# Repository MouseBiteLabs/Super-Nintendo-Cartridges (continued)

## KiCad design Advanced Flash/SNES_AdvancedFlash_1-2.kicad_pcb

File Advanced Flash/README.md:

# Super Nintendo Advanced Flash Cartridge (SNES-8XJ4D-01A)

# Order at your own risk -- v1.2 is technically untested, but previous version is fully tested

This is a new and improved Super Nintendo cartridge circuit board design that is capable of being flashed via the <a href="https://github.com/sanni/cartreader">Open Source Cart Reader (OSCR) by sanni</a>. Alternatively, you can also flash the ROM chips before soldering them to the board through the use of a programmer like the <a href="https://xgecu.myshopify.com/products/xgecu-new-t48-tl866-3gprogrammer-v12-01-support-28000-ics-for-spi-nor-nand-flash-emmc-bga153-162-169-100-221-tsop-sop-plcc">T48 programmer</a> with the <a href="https://xgecu.myshopify.com/products/100-original-xgecu-adp_f48_ex-1-tsop48-special-adapter-for-nor-flash-only-use-on-t48-tl866-3g-programmer">TSOP48 adapter</a>. This cartridge is made entirely from **brand new off the shelf components.** No donors are required, and you don't need to rely on AliExpress or eBay for parts!

This cartridge covers over 95% of the entire SNES library, capable of any standard cartridge **but not those with co-processors, such as SA-1 or SuperFX.** You can backup games onto it with the following settings:
- All memory maps supported: LoROM, HiROM, ExLoROM, and ExHiROM
- Can be programmed to operate as a multicart, changing games by pressing the SNES reset button (this includes the ability to make two games of the same memory map, or one of each)
- Up to 8 MB of ROM space for a single game or 4 MB of ROM space for two games
- Up to 32 KB of RAM space for a single game or two separate banks of 32 KB RAM space for two games
- All these settings can be changed via DIP switch for easy on-the-fly modifications without soldering

All gerbers and source files can be found in this repo, as this project is fully open source. Please read all instructions before attempting the project.

## Important Things Before You Start

1) <a href="https://github.com/MouseBiteLabs/Super-Nintendo-Cartridges/wiki">Please review the wiki for more information about using the circuit boards, instructions for how to program them, and example builds.</a>
2) When soldering parts on, it's a good idea to put kapton tape or otherwise cover the bottom cartridge edge. You do not want to get solder on the cartridge contacts.
3) I am not responsible for any damage you do to your self or your property. Attempt this project at your own risk.
4) I do not guarantee design compatibility. You may encounter issues with certain games. There is also a chance I have made an error in the design or the BOM - if this is the case, I will do everything I can to address the problem as quickly as possible.
5) If you are using this board to make games other than for personal use, you must have permission from the originator to use and distribute any ROM images or other related material. You are responsible for making sure you adhere to any license requirements.

DO NOT use my circuit boards for profiting from stolen work - this especially includes homebrew content, ROM hacks, and using fan-made labels without permission from the originator. **Support ALL original creators!**

## Board Characteristics and Order Information

The zipped folder contains all the gerber files for this board. The following options **must** be chosen when ordering boards for yourself.

- Thickness: 1.2mm
- Surface Finish: ENIG
- Gold Fingers: Yes, 30° chamfer

You can use the zipped folder at any board fabricator you like. You may also buy the board from PCBWay using this link (disclosure: I receive 10% of the sale value to go towards future PCB orders of my own):

### Purchase from My Website

You can purchase this circuit board at my website, [https://mousebitelabs.store](https://mousebitelabs.store). Click the following image to be directed to the specific item listing:

### Purchase from Etsy

I also offer the board on Etsy, if you would rather purchase through there - click the banner to be redirected.

### Purchase from insideGadgets

And finally, insideGadgets sells these boards fully populated!

## Required Equipment

- You will need basic tools, like a soldering iron, hot plate, and/or hot air rework station.
- You need a way to program the ROM chip(s).
  - This can be done with the <a href="https://github.com/sanni/cartreader">OSCR</a> to load the game and save data onto the catridge, after the cartridge is assembled.
  - Another option is to use insideGadgets' <a href="https://shop.insidegadgets.com/product/snesxflasher/">SNES programmer</a> made specifically for my cartridges. <a href="https://shop.insidegadgets.com/product/snes-advanced-flash-cartridge/">You can even purchase assembled boards from them!</a>
  - Alternatively, the <a href="https://xgecu.myshopify.com/products/xgecu-new-t48-tl866-3gprogrammer-v12-01-support-28000-ics-for-spi-nor-nand-flash-emmc-bga153-162-169-100-221-tsop-sop-plcc">T48 programmer</a> with the <a href="https://xgecu.myshopify.com/products/100-original-xgecu-adp_f48_ex-1-tsop48-special-adapter-for-nor-flash-only-use-on-t48-tl866-3g-programmer">TSOP48 adapter</a> can program the ROM chip(s). The downside to this is that if you screw up the programming, you'll have to desolder the chips and program them again.
- This cartridge uses the PIC12F629 with the <a href="https://sd2snes.de/blog/cool-stuff/supercic">SuperCIC code</a> to fake out the lockout chip. You will need a way to program these PIC chips. I use the T48 to do so, but you can also use something like the <a href="https://www.microchip.com/en-us/development-tool/pg164130">PICkit 3.</a> Note that if you have region modded your SNES, you won't need the lockout chips in the cartridges.

## How to Program

<a href="https://github.com/MouseBiteLabs/Super-Nintendo-Cartridges/wiki/Preparing-the-ROM">Please check out the wiki pages on how to prepare the ROM and program the cartridge.</a>

## Board Configurations

You *do not* need every single part on this board to make a game. The game you want to make is mainly dependent on the memory mapping (LoROM, HiROM, etc), the ROM size, and the RAM size. Depending on your needs, you only need to solder on certain components, which you can find below in the BOM section.

- **Every board needs Group A components.** You can make LoRom or HiROM games that have no RAM and are up to 4 MB large with this configuration. (If your game is only 2 MB, you do not need to include U9 and C9)
- If you need RAM space, **add Group B components.** This will add 32 KB of RAM space. (Multicarts will need the AS6C1008 chip for the RAM)
- If your game is larger than 4 MB, it will use the ExLoROM or ExHiROM memory mapping. **Add Group C components for this.**
- For multicarts, you can make a board with two games on it up to 4 MB each. You will need Group C components, **as well as Group D components.** (If one of the two games you want to program is only 2 MB, you do not need to include U9 and C9 for Game 1, and/or U12 and C12 for Game 2.)

## Switches

For SW1 through SW5, you can either use the DIP switch as indicated in the BOM below (in the "Optional" sections), or you can jumper the pads underneath the switch to turn the switch "ON". In this example, positions 1 and 2 are "ON"; 3 and 4 are "OFF":

### Switch 1 - Memory Mapping

This is the LoROM/HiROM switch. Turn it on to enter LoROM mode, or turn it off for HiROM mode, depending on the game you program.

### Switch 2 - SRAM Size

This sets the RAM size for the game, assuming you have the RAM chip installed. The maximum allocated RAM space *per game* on this board is only 32 KB, even if you put a 128 KB RAM chip (you will need the 128 KB chip for multicarts). Some games will care that you have the correct RAM size, or else they will activate piracy protection, so you should try to match the settings your game calls for. Note that DIP positions 1/2, and 3/4 should be changed together simultaneously:

- For 2 KB of RAM, set all switches OFF.
- For 8 KB of RAM, set positions 1 and 2 ON, and 3 and 4 OFF.
- For 32 KB of RAM, set all positions ON.

*Note: If you have a v1.1 board, please read the section below, as the instructions are slightly different to set the RAM size correctly.*

### Switch 3 - Ex Mode

Switch this ON to change the setting on SW1 to ExLoROM/ExHiROM. Switch it OFF to keep SW1 as a LoROM/HiROM switch.

### Switch 4 and 5 - Multicart Configurations

These two sets of switches control the multicart features on the board. You can make two LoROM games, two HiROM games, or one LoROM game and one HiROM game if you set the "Map Swap" switch to "YES". Here is how to use the switches to program the two games:

- Set SW4B (MULTI MODE) to "PRG" (for programming)
- Put SW4A (MAP SWAP) in the mode you want to use:
  - YES = Game 1 is LoROM, Game 2 is HiROM
  - NO = Game 1 and Game 2 are both LoROM or HiROM depending on SW1 position
  - If you are programming two of the same memory map types, put SW1 into the desired memory map mode (SW1 position does not matter if you are using the map swap feature)
- Program the first game by putting SW5 in "GAME 1" position; program the second by putting SW5 in "GAME 2" position
  - If you are going to use the map swap feature, make sure game 1 is the LoROM game and game 2 is the HiROM game!
- After both games are programmed, set SW4B to "PLAY"

Note that if you keep SW4B in "PRG" mode, the game that boots up will be determined by the position of SW5.

## Fix for v1.1

There's a minor issue with v1.1 of the board. **This does not affect versions after v1.1.** 

For setting the SRAM size using SW2, you must do the following:

- For 2 KB of RAM, set all switches OFF.
- For 8 KB of RAM, set positions 1 and 2 ON, and 3 and 4 OFF. **REMOVE R8 AND R9 FROM THE BOARD.**
- For 32 KB of RAM, set all positions ON. **REMOVE R8, R9, R10, AND R11 FROM THE BOARD.**

If you *do not* remove the resistors as defined above, your save battery life will be severely impacted. 

### Multicarts for v1.1

You *cannot* make multicarts on v1.1.

## Estimating Battery Life

To accurately estimate the battery life, you must first solder the battery in, and then either program your game in the OSCR or power it on in a Super Nintendo.

After that, measure the voltage across R1 using a multimeter in DC mV mode, touching the probes to the two test point pads on either side of R1 (or, the + and - pads on the back of the board below my smiling face). You should read something around 10 mV or less. If you are severely higher than 10 mV, like in the 100's of mV, then you have a problem on your board.

Once you have a suitable voltage, find the milliamp-hour rating of your selected battery (preferrably from a datasheet). For example, a Renata CR2032 battery is rated for 225 mAh.

Now to estimate battery life, take the voltage measurement in mV and the battery rating in mAh, and plug it into this equation: 

Time (years) = Resistance of R1 (ohms) * Battery capacity (mAh) / Voltage (mV) / 8760

The factor of 8760 is for converting years to hours (24 hours in a day, 365 days in a year). The resistance of R1 is 10000 ohms. So for an example, if you measured 10 mV on R1 and are using a Renata CR2032, you would get 10000 * 225 / 10 / 8760 = **25.7 years.**

## Troubleshooting

<a href="https://github.com/MouseBiteLabs/Super-Nintendo-Cartridges/wiki/Troubleshooting-Tips">Please check out the wiki pages for troubleshooting tips.</a>

## Bill of Materials (BOM)

The component groups required for the build you want to make are detailed above. Note that the "optional" groups mostly only contain the switches, as you can manually set the switch position with a 0-ohm resistor (or, lack of a resistor). Remember, shorting the pads means the switch is ON, and keeping the pads depopulated means the switch is OFF.

### Mouser Shopping Cart

The following cart has *the maximum amount* of parts you would potentially need on a single board (essentially, a multicart), plus a few extras of the passive components due to price breaks. This also includes **four M29F160 chips and both the AS6C62256 and AS6C1008.** You can remove the chips you don't need from the shopping cart before ordering, according to the component group assignments below.

https://www.mouser.com/ProjectManager/ProjectDetail.aspx?AccessID=1bc68cfc83

### Group A - 4 MB ROM, No RAM

Note: If your game is only 2 MB, you do not need U9 and C9.

| Reference | Value/Part Number | Package       | Description      | Source                                           |
| --------- | ----------------- | ------------- | ---------------- | ------------------------------------------------ |
| C1        | 0.1u              | 0603          | Capacitor (MLCC) | [https://mou.sr/3ENc15O](https://mou.sr/3ENc15O) |
| C2        | 0.1u              | 0603          | Capacitor (MLCC) | [https://mou.sr/3ENc15O](https://mou.sr/3ENc15O) |
| C3        | 0.1u              | 0603          | Capacitor (MLCC) | [https://mou.sr/3ENc15O](https://mou.sr/3ENc15O) |
| C4        | 0.1u              | 0603          | Capacitor (MLCC) | [https://mou.sr/3ENc15O](https://mou.sr/3ENc15O) |
| C7        | 0.1u              | 0603          | Capacitor (MLCC) | [https://mou.sr/3ENc15O](https://mou.sr/3ENc15O) |
| C8        | 0.1u              | 0603          | Capacitor (MLCC) | [https://mou.sr/3ENc15O](https://mou.sr/3ENc15O) |
| C9        | 0.1u              | 0603          | Capacitor (MLCC) | [https://mou.sr/3ENc15O](https://mou.sr/3ENc15O) |
| CC        | 22u               | 1206          | Capacitor (MLCC) | [https://mou.sr/4e4zShm](https://mou.sr/4e4zShm) |
| R2        | 100k              | 0603          | Resistor         | [https://mou.sr/49bgMnu](https://mou.sr/49bgMnu) |
| R3        | 10k               | 0603          | Resistor         | [https://mou.sr/3riR7IH](https://mou.sr/3riR7IH) |
| R4        | 100k              | 0603          | Resistor         | [https://mou.sr/49bgMnu](https://mou.sr/49bgMnu) |
| R5        | 10k               | 0603          | Resistor         | [https://mou.sr/3riR7IH](https://mou.sr/3riR7IH) |
| U1        | PIC12F629         | DIP-8, SOIC-8 | Lockout Chip     | [https://mou.sr/3XuEZzO](https://mou.sr/3XuEZzO) |
| U2        | SN74CBT3257CPWR   | TSSOP-16      | Multiplexer      | [https://mou.sr/3MKJwd1](https://mou.sr/3MKJwd1) |
| U3        | SN74CBT3257CPWR   | TSSOP-16      | Multiplexer      | [https://mou.sr/3MKJwd1](https://mou.sr/3MKJwd1) |
| U4        | SN74CBT3257CPWR   | TSSOP-16      | Multiplexer      | [https://mou.sr/3MKJwd1](https://mou.sr/3MKJwd1) |
| U7        | 74HCT139          | TSSOP-16      | Decoder          | [https://mou.sr/4eqzppn](https://mou.sr/4eqzppn) |
| U8        | M29F160           | TSOP-48       | Flash EEPROM     | [https://mou.sr/3MNWQ0b](https://mou.sr/3MNWQ0b) |
| U9        | M29F160           | TSOP-48       | Flash EEPROM     | [https://mou.sr/3MNWQ0b](https://mou.sr/3MNWQ0b) |

### Group A (Optional) - Programming header, Lo/Hi switch/jumper

Note: J1 is a space that allows you to program the PIC using the standard ISP pinout while the chip is on-board. It is not a required component. If you wish to use it, you will need to pick out a component yourself to use here, as there are different ways to go about using it.

| Reference | Value/Part Number   | Package                  | Description        | Source                                           |
| --------- | ------------------- | ------------------------ | ------------------ | ------------------------------------------------ |
| J1        | \--                 | 2x3 pins, 2.54mm spacing | Header (see note)  | N/A                                              |
| RS1       | 0 ohm               | 0603                     | Resistor (Jumper)  | [https://mou.sr/4e1ABQg](https://mou.sr/4e1ABQg) |
| SW1       | DS04-254-2-01BK-SMT | 1-position DIP           | DIP Switch (1-pos) | [https://mou.sr/3MK4Lvz](https://mou.sr/3MK4Lvz) |

### Group B - adds 32 KB of RAM

Note: If you are making a multicart, you must use the AS6C1008 for U10.

| Reference | Value/Part Number   | Package        | Description        | Source                                           |
| --------- | ------------------- | -------------- | ------------------ | ------------------------------------------------ |
| B1        | CR2032              | CR2032         | Coin Cell Battery  | [https://mou.sr/3Wj2m0G](https://mou.sr/3Wj2m0G) |
| C5        | 0.1u                | 0603           | Capacitor (MLCC)   | [https://mou.sr/3ENc15O](https://mou.sr/3ENc15O) |
| C6        | 0.1u                | 0603           | Capacitor (MLCC)   | [https://mou.sr/3ENc15O](https://mou.sr/3ENc15O) |
| C10       | 0.1u                | 0603           | Capacitor (MLCC)   | [https://mou.sr/3ENc15O](https://mou.sr/3ENc15O) |
| C11       | 0.1u                | 0603           | Capacitor (MLCC)   | [https://mou.sr/3ENc15O](https://mou.sr/3ENc15O) |
| CB        | 22u                 | 1206           | Capacitor (MLCC)   | [https://mou.sr/4e4zShm](https://mou.sr/4e4zShm) |
| Q1        | 2N7002              | SOT-23         | N-channel MOSFET   | [https://mou.sr/3rgfh6J](https://mou.sr/3rgfh6J) |
| R1        | 10k                 | 0603           | Resistor           | [https://mou.sr/3riR7IH](https://mou.sr/3riR7IH) |
| R6        | 130k                | 0603           | Resistor           | [https://mou.sr/3MjXliy](https://mou.sr/3MjXliy) |
| R7        | 49.9k               | 0603           | Resistor           | [https://mou.sr/3BBcDgp](https://mou.sr/3BBcDgp) |
| R8        | 100k                | 0603           | Resistor           | [https://mou.sr/49bgMnu](https://mou.sr/49bgMnu) |
| R9        | 100k                | 0603           | Resistor           | [https://mou.sr/49bgMnu](https://mou.sr/49bgMnu) |
| R10       | 100k                | 0603           | Resistor           | [https://mou.sr/49bgMnu](https://mou.sr/49bgMnu) |
| R11       | 100k                | 0603           | Resistor           | [https://mou.sr/49bgMnu](https://mou.sr/49bgMnu) |
| U5        | 74HCT139            | TSSOP-16       | Decoder            | [https://mou.sr/4eqzppn](https://mou.sr/4eqzppn) |
| U6        | 74HCT139            | TSSOP-16       | Decoder            | [https://mou.sr/4eqzppn](https://mou.sr/4eqzppn) |
| U10       | AS6C62256, AS6C1008 | SOP-28, SOP-32 | SRAM               | [https://mou.sr/3ZxG6jd](https://mou.sr/3ZxG6jd) |
| U11       | TPS3613             | MSOP-10        | Battery Management | [https://mou.sr/45Ir2kh](https://mou.sr/45Ir2kh) |

### Group B (Optional) - RAM size switch/jumpers

| Reference | Value/Part Number   | Package        | Description        | Source                                           |
| --------- | ------------------- | -------------- | ------------------ | ------------------------------------------------ |
| RS2A      | 0 ohm               | 0603           | Resistor (Jumper)  | [https://mou.sr/4e1ABQg](https://mou.sr/4e1ABQg) |
| RS2B      | 0 ohm               | 0603           | Resistor (Jumper)  | [https://mou.sr/4e1ABQg](https://mou.sr/4e1ABQg) |
| RS2C      | 0 ohm               | 0603           | Resistor (Jumper)  | [https://mou.sr/4e1ABQg](https://mou.sr/4e1ABQg) |
| RS2D      | 0 ohm               | 0603           | Resistor (Jumper)  | [https://mou.sr/4e1ABQg](https://mou.sr/4e1ABQg) |
| SW2       | DS04-254-2-04BK-SMT | 4-position DIP | DIP Switch (4-pos) | [https://mou.sr/3MPsI4o](https://mou.sr/3MPsI4o) |

### Group C - Adds 4 MB ROM for ExLoROM and ExHiROM

Note: If your Ex-mode game is 6 MB large, you don't need U13 and C13.

| Reference | Value/Part Number | Package | Description      | Source                                           |
| --------- | ----------------- | ------- | ---------------- | ------------------------------------------------ |
| C12       | 0.1u              | 0603    | Capacitor (MLCC) | [https://mou.sr/3ENc15O](https://mou.sr/3ENc15O) |
| C13       | 0.1u              | 0603    | Capacitor (MLCC) | [https://mou.sr/3ENc15O](https://mou.sr/3ENc15O) |
| U12       | M29F160           | TSOP-48 | Flash EEPROM     | [https://mou.sr/3MNWQ0b](https://mou.sr/3MNWQ0b) |
| U13       | M29F160           | TSOP-48 | Flash EEPROM     | [https://mou.sr/3MNWQ0b](https://mou.sr/3MNWQ0b) |

### Group C (Optional) - Ex Mode switch/jumper

| Reference | Value/Part Number   | Package        | Description        | Source                                           |
| --------- | ------------------- | -------------- | ------------------ | ------------------------------------------------ |
| RS3       | 0 ohm               | 0603           | Resistor (Jumper)  | [https://mou.sr/4e1ABQg](https://mou.sr/4e1ABQg) |
| SW3       | DS04-254-2-01BK-SMT | 1-position DIP | DIP Switch (1-pos) | [https://mou.sr/3MK4Lvz](https://mou.sr/3MK4Lvz) |

### Group D - Enables multicart mode

Note: If your game(s) are 2 MB, you do not need U9 and C9 (for Game 1) and/or U12 and C12 (for Game 2).

| Reference | Value/Part Number | Package   | Description      | Source                                           |
| --------- | ----------------- | --------- | ---------------- | ------------------------------------------------ |
| C14       | 0.1u              | 0603      | Capacitor (MLCC) | [https://mou.sr/3ENc15O](https://mou.sr/3ENc15O) |
| R13       | 1k                | 0603      | Resistor         | [https://mou.sr/3U0EvS4](https://mou.sr/3U0EvS4) |
| U14       | 74HCT74           | TSSOP-14  | Flip-Flop        | [https://mou.sr/4eroZpu](https://mou.sr/4eroZpu) |

### Group D (Optional) - Multicart mode switches/jumpers

| Reference | Value/Part Number   | Package        | Description        | Source                                           |
| --------- | ------------------- | -------------- | ------------------ | ------------------------------------------------ |
| RS4A      | 0 ohm               | 0603           | Resistor (Jumper)  | [https://mou.sr/4e1ABQg](https://mou.sr/4e1ABQg) |
| RS4B      | 0 ohm               | 0603           | Resistor (Jumper)  | [https://mou.sr/4e1ABQg](https://mou.sr/4e1ABQg) |
| RS5       | 0 ohm               | 0603           | Resistor (Jumper)  | [https://mou.sr/4e1ABQg](https://mou.sr/4e1ABQg) |
| SW4       | DS04-254-2-02BK-SMT | 2-position DIP | DIP Switch (2-pos) | [https://mou.sr/3B7BqZr](https://mou.sr/3B7BqZr) |
| SW5       | DS04-254-2-01BK-SMT | 1-position DIP | DIP Switch (1-pos) | [https://mou.sr/3MK4Lvz](https://mou.sr/3MK4Lvz) |

## Revision History

### v1.2 - Release

- Fixed C9 and C12 positions on PCB
- Added resistors under all switches as alternative
- Changed R8 through R11 to pull-down resistors
- Added Q1 to ensure RAM start-up at correct time
- Simplified multicart circuit to reduce battery current draw, lower the BOM count/cost and simplify the design
- Remove "1" from single DIP switches for clarity

### v1.1 - Beta

- Change reference designators CC1 to CC, CB1 to CB
- Make silkscreen thicker, pin 1 indicators bigger, add boxes around passives
- Round the cart edge for easier insertion, add cart edge pin numbers
- Add pin 1 indicators to switches and U1; move U2-U7 reference designators
- Change Prog/Play to more descriptive language
- Add pads for resistors instead of switches

### v1.0 - Alpha

- Prototype version

## Acknowledgements

- Extremely huge thanks to sanni for firstly creating the OSCR, and secondly for adding programming support for the cartridges.
- Continual thanks to all in the nesdev community for their resources, design tips, and support throughout the past half-decade.

## License

<br />This work is licensed under a <a rel="license" href="http://creativecommons.org/licenses/by-sa/4.0/">Creative Commons Attribution-ShareAlike 4.0 International License</a>. You are able to copy and redistribute the material in any medium or format, as well as remix, transform, or build upon the material for any purpose (even commercial) - but you **must** give appropriate credit, provide a link to the license, and indicate if any changes were made.

©MouseBiteLabs 2024

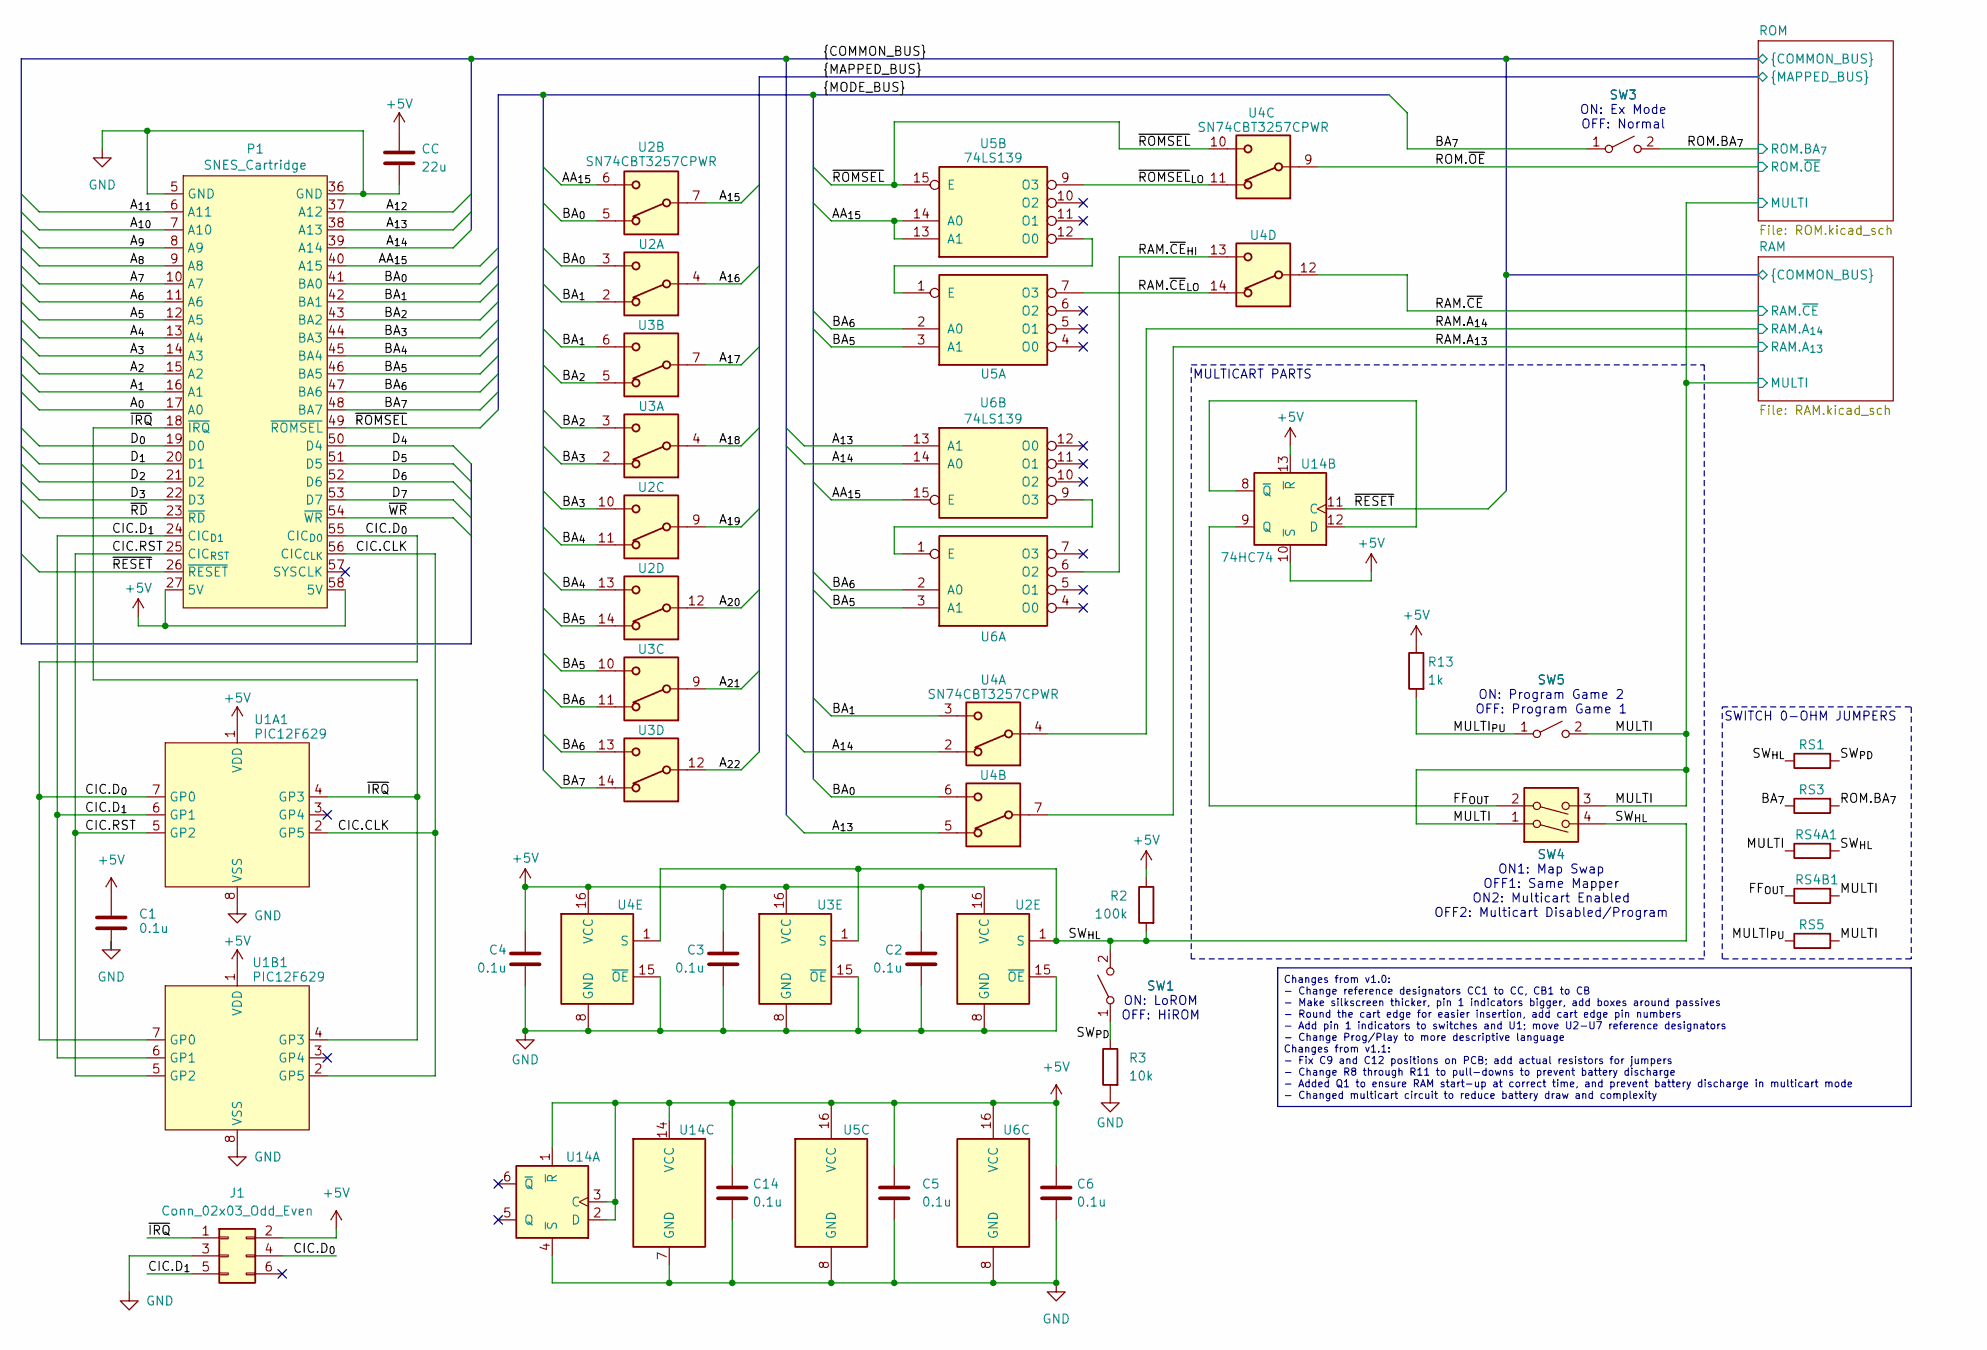
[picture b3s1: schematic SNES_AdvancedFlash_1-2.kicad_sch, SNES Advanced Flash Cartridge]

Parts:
C1, C2, C3, C4, C5, C6, C14: 0.1u; C_0603_1608Metric_Boxed
CC: 22u; C_1206_3216Metric_Boxed
J1: Conn_02x03_Odd_Even; PinHeader_2x03_P2.54mm_Vertical
P1: SNES_Cartridge; Cart_Edge_SNES_Standard
R2: 100k; R_0603_1608Metric_Boxed
R3: 10k; R_0603_1608Metric_Boxed
R13: 1k; R_0603_1608Metric_Boxed
RS1, RS3, RS4A1, RS4B1, RS5: 0; R_0603_1608Metric_NoSilk
SW1, SW3, SW5: SW_SPST; SPST_SMT
SW4: SW_DIP_x02; SPSTx2_SMT
U1A1: PIC12F629; SOIC-8W_5.3x5.3mm_P1.27mm
U1B1: PIC12F629; DIP-8_W7.62mm
U2, U3, U4: SN74CBT3257CPWR; TSSOP-16_4.4x5mm_P0.65mm
U5, U6: 74LS139; TSSOP-16_4.4x5mm_P0.65mm
U14: 74HC74; TSSOP-14_4.4x5mm_P0.65mm

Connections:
+5V: C1.1, C2.1, C3.1, C4.1, C5.1, C6.1, C14.1, CC.1, J1.2, P1.27 (5V), P1.58 (5V), R2.1, R13.1, U1A1.1 (VDD), U1B1.1 (VDD), U2.16 (VCC), U3.16 (VCC), U4.16 (VCC), U5.16 (VCC), U6.16 (VCC), U14.1 (~R), U14.2 (D), U14.3 (C), U14.10 (~S), U14.13 (~R), U14.14 (VCC); also elsewhere on the board
/AA_{15}: P1.40 (A15), U2.6, U5.13 (A1), U5.14 (A0), U6.15 (E)
/A_{0}: P1.17 (A0); also elsewhere on the board
/A_{1}: P1.16 (A1); also elsewhere on the board
/A_{2}: P1.15 (A2); also elsewhere on the board
/A_{3}: P1.14 (A3); also elsewhere on the board
/A_{4}: P1.13 (A4); also elsewhere on the board
/A_{5}: P1.12 (A5); also elsewhere on the board
/A_{6}: P1.11 (A6); also elsewhere on the board
/A_{7}: P1.10 (A7); also elsewhere on the board
/A_{8}: P1.9 (A8); also elsewhere on the board
/A_{9}: P1.8 (A9); also elsewhere on the board
/A_{10}: P1.7 (A10); also elsewhere on the board
/A_{11}: P1.6 (A11); also elsewhere on the board
/A_{12}: P1.37 (A12); also elsewhere on the board
/A_{13}: P1.38 (A13), U4.5, U6.13 (A1); also elsewhere on the board
/A_{14}: P1.39 (A14), U4.2, U6.14 (A0); also elsewhere on the board
/A_{15}: U2.7; also elsewhere on the board
/A_{16}: U2.4; also elsewhere on the board
/A_{17}: U3.7; also elsewhere on the board
/A_{18}: U3.4; also elsewhere on the board
/A_{19}: U2.9; also elsewhere on the board
/A_{20}: U2.12; also elsewhere on the board
/A_{21}: U3.9; also elsewhere on the board
/A_{22}: U3.12
/BA_{0}: P1.41 (BA0), U2.3, U2.5, U4.6
/BA_{1}: P1.42 (BA1), U2.2, U3.6, U4.3
/BA_{2}: P1.43 (BA2), U3.3, U3.5
/BA_{3}: P1.44 (BA3), U2.10, U3.2
/BA_{4}: P1.45 (BA4), U2.11, U2.13
/BA_{5}: P1.46 (BA5), U2.14, U3.10, U5.3 (A1), U6.3 (A1)
/BA_{6}: P1.47 (BA6), U3.11, U3.13, U5.2 (A0), U6.2 (A0)
/BA_{7}: P1.48 (BA7), RS3.1, SW3.1 (A), U3.14
/CIC.CLK: P1.56 (CIC_{CLK}), U1A1.2 (GP5), U1B1.2 (GP5)
/CIC.D_{0}: J1.4, P1.55 (CIC_{D0}), U1A1.7 (GP0), U1B1.7 (GP0)
/CIC.D_{1}: J1.5, P1.24 (CIC_{D1}), U1A1.6 (GP1), U1B1.6 (GP1)
/CIC.RST: P1.25 (CIC_{RST}), U1A1.5 (GP2), U1B1.5 (GP2)
/D_{0}: P1.19 (D0); also elsewhere on the board
/D_{1}: P1.20 (D1); also elsewhere on the board
/D_{2}: P1.21 (D2); also elsewhere on the board
/D_{3}: P1.22 (D3); also elsewhere on the board
/D_{4}: P1.50 (D4); also elsewhere on the board
/D_{5}: P1.51 (D5); also elsewhere on the board
/D_{6}: P1.52 (D6); also elsewhere on the board
/D_{7}: P1.53 (D7); also elsewhere on the board
/FF_{OUT}: RS4B1.1, SW4.2, U14.9 (Q)
/MULTI: RS4A1.1, RS4B1.2, RS5.2, SW4.1, SW4.3, SW5.2 (B); also elsewhere on the board
/MULTI_{PU}: R13.2, RS5.1, SW5.1 (A)
/RAM.A_{13}: U4.7; also elsewhere on the board
/RAM.A_{14}: U4.4; also elsewhere on the board
/RAM.~CE: U4.12; also elsewhere on the board
/RAM.~CE_{HI}: U4.13, U6.6 (O2)
/RAM.~CE_{LO}: U4.14, U5.7 (O3)
/ROM.BA_{7}: RS3.2, SW3.2 (B); also elsewhere on the board
/ROM.~OE: U4.9; also elsewhere on the board
/SW_{HL}: R2.2, RS1.1, RS4A1.2, SW1.2 (B), SW4.4, U2.1 (S), U3.1 (S), U4.1 (S)
/SW_{PD}: R3.1, RS1.2, SW1.1 (A)
/~IRQ: J1.1, P1.18 (~IRQ), U1A1.4 (GP3), U1B1.4 (GP3)
/~RD: P1.23 (~RD); also elsewhere on the board
/~RESET: P1.26 (~RESET), U14.11 (C); also elsewhere on the board
/~ROMSEL: P1.49 (~ROMSEL), U4.10, U5.15 (E)
/~ROMSEL_{LO}: U4.11, U5.9 (O3)
/~WR: P1.54 (~WR); also elsewhere on the board
GND: C1.2, C2.2, C3.2, C4.2, C5.2, C6.2, C14.2, CC.2, J1.3, P1.5 (GND), P1.36 (GND), R3.2, U1A1.8 (VSS), U1B1.8 (VSS), U2.8 (GND), U2.15 (~OE), U3.8 (GND), U3.15 (~OE), U4.8 (GND), U4.15 (~OE), U5.8 (GND), U6.8 (GND), U14.4 (~S), U14.7 (GND); also elsewhere on the board
unnamed: U5.1 (E), U5.12 (O0)
unnamed: U6.1 (E), U6.9 (O3)
unnamed: U14.8 (~Q), U14.12 (D)

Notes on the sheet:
SW1 ON: LoROM OFF: HiROM
SWITCH 0-OHM JUMPERS
Changes from v1.0: - Change reference designators CC1 to CC, CB1 to CB - Make silkscreen thicker, pin 1 indicators bigger, add boxes around passives - Round the cart edge for easier insertion, add cart edge pin numbers - Add pin 1 indicators to switches and U1; move U2-U7 reference designators - Ch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
SW3 ON: Ex Mode OFF: Normal
SW5 ON: Program Game 2 OFF: Program Game 1
MULTICART PARTS
SW4 ON1: Map Swap OFF1: Same Mapper ON2: Multicart Enabled OFF2: Multicart Disabled/Program

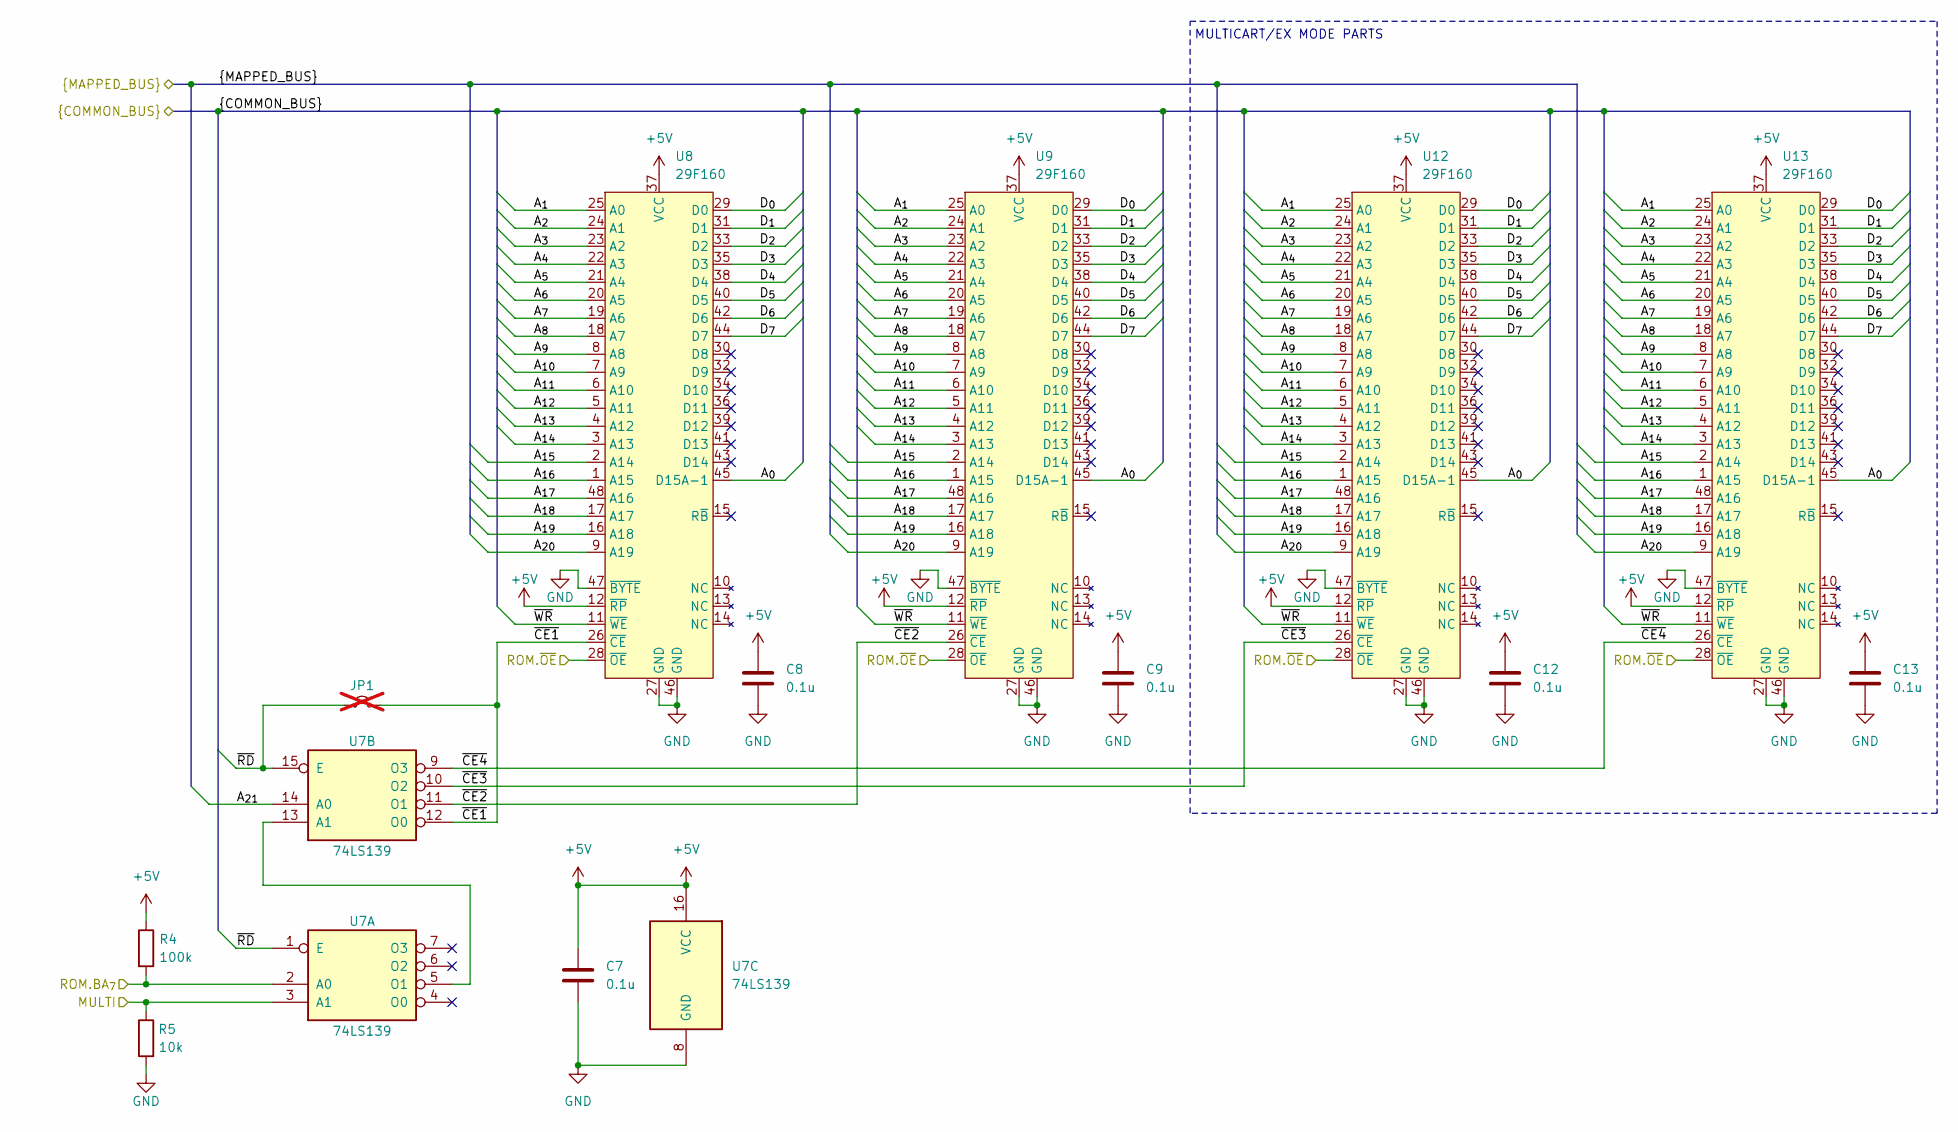
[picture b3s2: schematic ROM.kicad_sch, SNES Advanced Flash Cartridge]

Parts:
C7, C8, C9, C12, C13: 0.1u; C_0603_1608Metric_Boxed
JP1: Jumper_2_Small_Open; SolderJumper-2_P1.3mm_Open_Pad1.0x1.5mm; not fitted
R4: 100k; R_0603_1608Metric_Boxed
R5: 10k; R_0603_1608Metric_Boxed
U7: 74LS139; TSSOP-16_4.4x5mm_P0.65mm
U8, U9, U12, U13: 29F160; TSOP-I-48_18.4x12mm_P0.5mm

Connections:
+5V: C7.1, C8.1, C9.1, C12.1, C13.1, R4.1, U7.16 (VCC), U8.12 (~RP), U8.37 (VCC), U9.12 (~RP), U9.37 (VCC), U12.12 (~RP), U12.37 (VCC), U13.12 (~RP), U13.37 (VCC); also elsewhere on the board
/A_{0}: U8.45 (D15A-1), U9.45 (D15A-1), U12.45 (D15A-1), U13.45 (D15A-1); also elsewhere on the board
/A_{1}: U8.25 (A0), U9.25 (A0), U12.25 (A0), U13.25 (A0); also elsewhere on the board
/A_{2}: U8.24 (A1), U9.24 (A1), U12.24 (A1), U13.24 (A1); also elsewhere on the board
/A_{3}: U8.23 (A2), U9.23 (A2), U12.23 (A2), U13.23 (A2); also elsewhere on the board
/A_{4}: U8.22 (A3), U9.22 (A3), U12.22 (A3), U13.22 (A3); also elsewhere on the board
/A_{5}: U8.21 (A4), U9.21 (A4), U12.21 (A4), U13.21 (A4); also elsewhere on the board
/A_{6}: U8.20 (A5), U9.20 (A5), U12.20 (A5), U13.20 (A5); also elsewhere on the board
/A_{7}: U8.19 (A6), U9.19 (A6), U12.19 (A6), U13.19 (A6); also elsewhere on the board
/A_{8}: U8.18 (A7), U9.18 (A7), U12.18 (A7), U13.18 (A7); also elsewhere on the board
/A_{9}: U8.8 (A8), U9.8 (A8), U12.8 (A8), U13.8 (A8); also elsewhere on the board
/A_{10}: U8.7 (A9), U9.7 (A9), U12.7 (A9), U13.7 (A9); also elsewhere on the board
/A_{11}: U8.6 (A10), U9.6 (A10), U12.6 (A10), U13.6 (A10); also elsewhere on the board
/A_{12}: U8.5 (A11), U9.5 (A11), U12.5 (A11), U13.5 (A11); also elsewhere on the board
/A_{13}: U8.4 (A12), U9.4 (A12), U12.4 (A12), U13.4 (A12); also elsewhere on the board
/A_{14}: U8.3 (A13), U9.3 (A13), U12.3 (A13), U13.3 (A13); also elsewhere on the board
/A_{15}: U8.2 (A14), U9.2 (A14), U12.2 (A14), U13.2 (A14); also elsewhere on the board
/A_{16}: U8.1 (A15), U9.1 (A15), U12.1 (A15), U13.1 (A15); also elsewhere on the board
/A_{17}: U8.48 (A16), U9.48 (A16), U12.48 (A16), U13.48 (A16); also elsewhere on the board
/A_{18}: U8.17 (A17), U9.17 (A17), U12.17 (A17), U13.17 (A17); also elsewhere on the board
/A_{19}: U8.16 (A18), U9.16 (A18), U12.16 (A18), U13.16 (A18); also elsewhere on the board
/A_{20}: U8.9 (A19), U9.9 (A19), U12.9 (A19), U13.9 (A19); also elsewhere on the board
/A_{21}: U7.14 (A0); also elsewhere on the board
/D_{0}: U8.29 (D0), U9.29 (D0), U12.29 (D0), U13.29 (D0); also elsewhere on the board
/D_{1}: U8.31 (D1), U9.31 (D1), U12.31 (D1), U13.31 (D1); also elsewhere on the board
/D_{2}: U8.33 (D2), U9.33 (D2), U12.33 (D2), U13.33 (D2); also elsewhere on the board
/D_{3}: U8.35 (D3), U9.35 (D3), U12.35 (D3), U13.35 (D3); also elsewhere on the board
/D_{4}: U8.38 (D4), U9.38 (D4), U12.38 (D4), U13.38 (D4); also elsewhere on the board
/D_{5}: U8.40 (D5), U9.40 (D5), U12.40 (D5), U13.40 (D5); also elsewhere on the board
/D_{6}: U8.42 (D6), U9.42 (D6), U12.42 (D6), U13.42 (D6); also elsewhere on the board
/D_{7}: U8.44 (D7), U9.44 (D7), U12.44 (D7), U13.44 (D7); also elsewhere on the board
/MULTI: R5.1, U7.3 (A1); also elsewhere on the board
/ROM.BA_{7}: R4.2, U7.2 (A0); also elsewhere on the board
/ROM.~OE: U8.28 (~OE), U9.28 (~OE), U12.28 (~OE), U13.28 (~OE); also elsewhere on the board
/ROM/~CE1: JP1.2 (B), U7.12 (O0), U8.26 (~CE)
/ROM/~CE2: U7.11 (O1), U9.26 (~CE)
/ROM/~CE3: U7.10 (O2), U12.26 (~CE)
/ROM/~CE4: U7.9 (O3), U13.26 (~CE)
/~RD: JP1.1 (A), U7.1 (E), U7.15 (E); also elsewhere on the board
/~WR: U8.11 (~WE), U9.11 (~WE), U12.11 (~WE), U13.11 (~WE); also elsewhere on the board
GND: C7.2, C8.2, C9.2, C12.2, C13.2, R5.2, U7.8 (GND), U8.27 (GND), U8.46 (GND), U8.47 (~BYTE), U9.27 (GND), U9.46 (GND), U9.47 (~BYTE), U12.27 (GND), U12.46 (GND), U12.47 (~BYTE), U13.27 (GND), U13.46 (GND), U13.47 (~BYTE); also elsewhere on the board
unnamed: U7.5 (O1), U7.13 (A1)

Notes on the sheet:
MULTICART/EX MODE PARTS

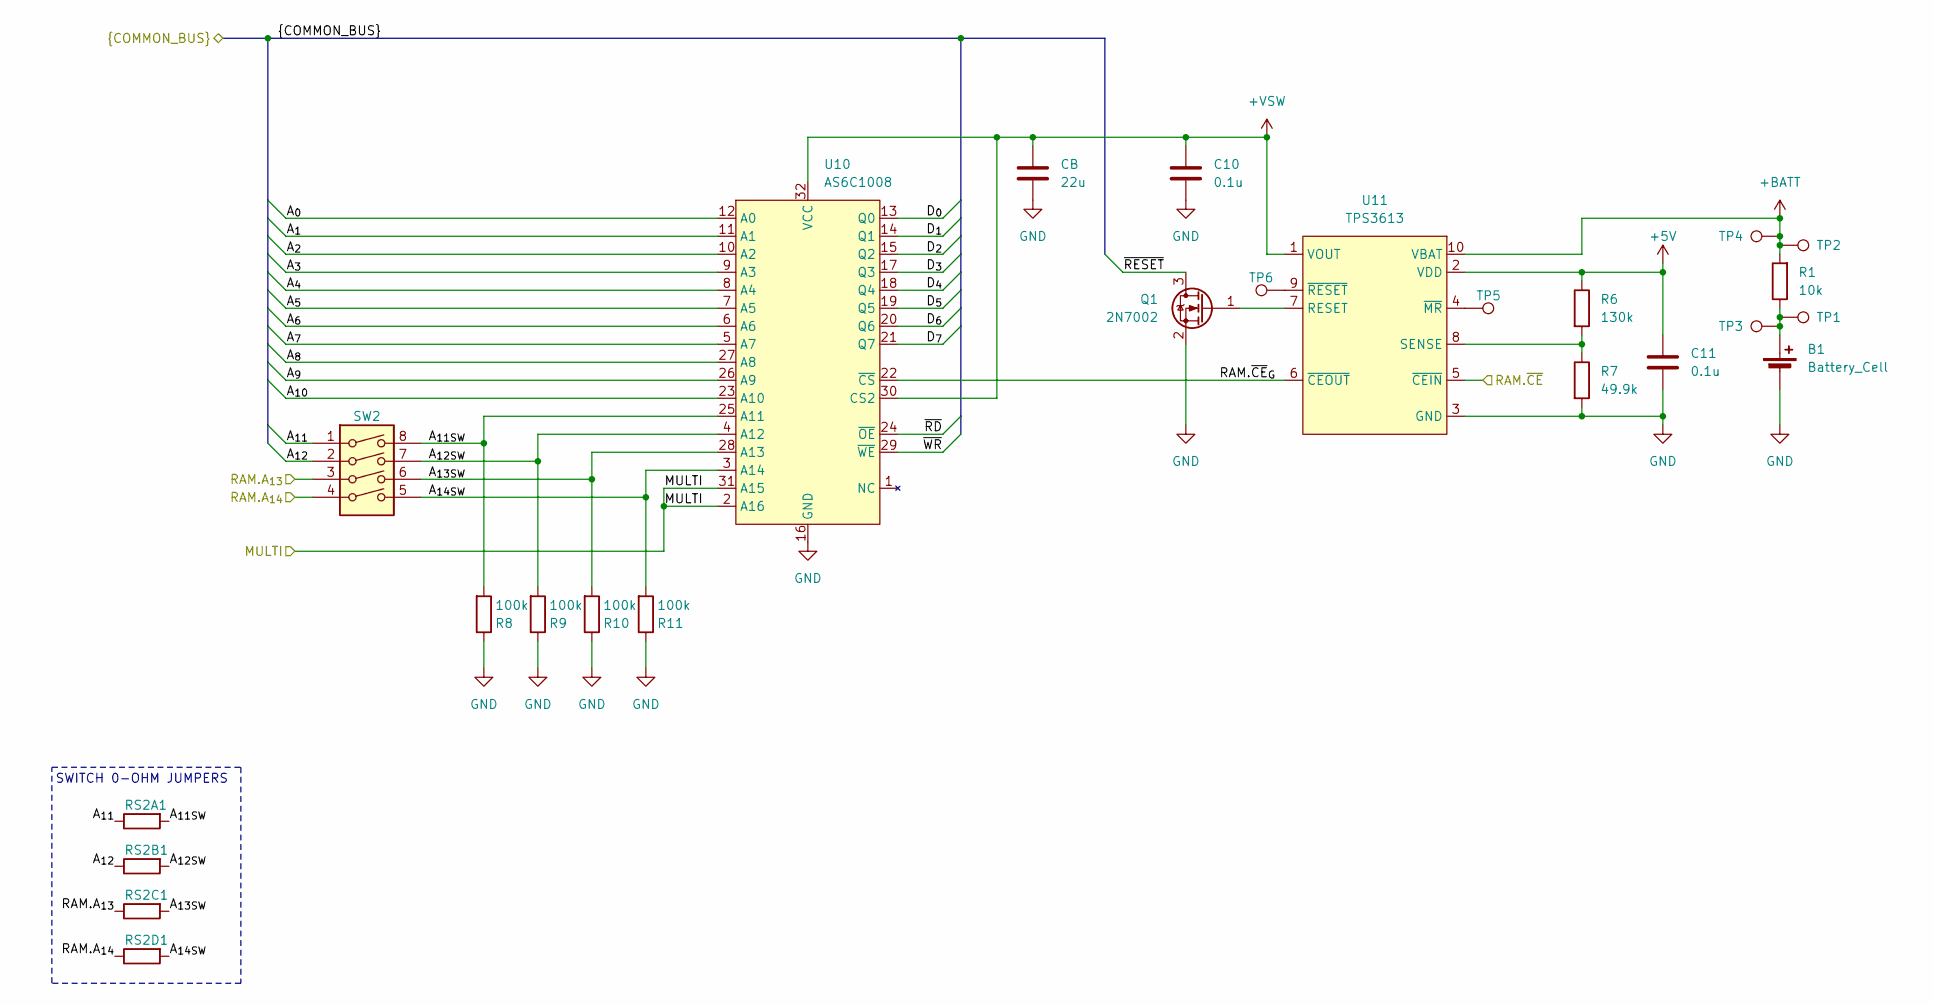
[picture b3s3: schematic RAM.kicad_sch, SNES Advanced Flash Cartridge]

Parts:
B1: Battery_Cell; CR_battery
C10, C11: 0.1u; C_0603_1608Metric_Boxed
CB: 22u; C_1206_3216Metric_Boxed
Q1: 2N7002; SOT-23
R1: 10k; R_0603_1608Metric_Boxed
R6: 130k; R_0603_1608Metric_Boxed
R7: 49.9k; R_0603_1608Metric_Boxed
R8, R9, R10, R11: 100k; R_0603_1608Metric_Boxed
RS2A1, RS2B1, RS2C1, RS2D1: 0; R_0603_1608Metric_NoSilk
SW2: SW_DIP_x04; SPSTx4_SMT
TP1, TP2, TP3, TP4, TP5, TP6: TestPoint; TestPoint_Pad_D1.0mm
U10: AS6C1008; SO32L_L
U11: TPS3613; MSOP-10_3x3mm_P0.5mm

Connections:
+5V: C11.1, R6.1, U11.2 (VDD); also elsewhere on the board
+BATT: R1.2, TP2.1, TP4.1, U11.10 (VBAT)
+VSW: C10.1, CB.1, U10.30 (CS2), U10.32 (VCC), U11.1 (VOUT)
/A_{0}: U10.12 (A0); also elsewhere on the board
/A_{1}: U10.11 (A1); also elsewhere on the board
/A_{2}: U10.10 (A2); also elsewhere on the board
/A_{3}: U10.9 (A3); also elsewhere on the board
/A_{4}: U10.8 (A4); also elsewhere on the board
/A_{5}: U10.7 (A5); also elsewhere on the board
/A_{6}: U10.6 (A6); also elsewhere on the board
/A_{7}: U10.5 (A7); also elsewhere on the board
/A_{8}: U10.27 (A8); also elsewhere on the board
/A_{9}: U10.26 (A9); also elsewhere on the board
/A_{10}: U10.23 (A10); also elsewhere on the board
/A_{11}: RS2A1.1, SW2.1; also elsewhere on the board
/A_{12}: RS2B1.1, SW2.2; also elsewhere on the board
/D_{0}: U10.13 (Q0); also elsewhere on the board
/D_{1}: U10.14 (Q1); also elsewhere on the board
/D_{2}: U10.15 (Q2); also elsewhere on the board
/D_{3}: U10.17 (Q3); also elsewhere on the board
/D_{4}: U10.18 (Q4); also elsewhere on the board
/D_{5}: U10.19 (Q5); also elsewhere on the board
/D_{6}: U10.20 (Q6); also elsewhere on the board
/D_{7}: U10.21 (Q7); also elsewhere on the board
/MULTI: U10.2 (A16), U10.31 (A15); also elsewhere on the board
/RAM.A_{13}: RS2C1.1, SW2.3; also elsewhere on the board
/RAM.A_{14}: RS2D1.1, SW2.4; also elsewhere on the board
/RAM.~CE: U11.5 (~CEIN); also elsewhere on the board
/RAM/A_{11SW}: R8.2, RS2A1.2, SW2.8, U10.25 (A11)
/RAM/A_{12SW}: R9.2, RS2B1.2, SW2.7, U10.4 (A12)
/RAM/A_{13SW}: R10.2, RS2C1.2, SW2.6, U10.28 (A13)
/RAM/A_{14SW}: R11.2, RS2D1.2, SW2.5, U10.3 (A14)
/RAM/RAM.~CE_{G}: U10.22 (~CS), U11.6 (~CEOUT)
/~RD: U10.24 (~OE); also elsewhere on the board
/~RESET: Q1.3 (D); also elsewhere on the board
/~WR: U10.29 (~WE); also elsewhere on the board
GND: B1.2 (-), C10.2, C11.2, CB.2, Q1.2 (S), R7.2, R8.1, R9.1, R10.1, R11.1, U10.16 (GND), U11.3 (GND); also elsewhere on the board
unnamed: B1.1 (+), R1.1, TP1.1, TP3.1
unnamed: Q1.1 (G), U11.7 (RESET)
unnamed: R6.2, R7.1, U11.8 (SENSE)
unnamed: TP5.1, U11.4 (~MR)
unnamed: TP6.1, U11.9 (~RESET)

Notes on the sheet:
SWITCH 0-OHM JUMPERS

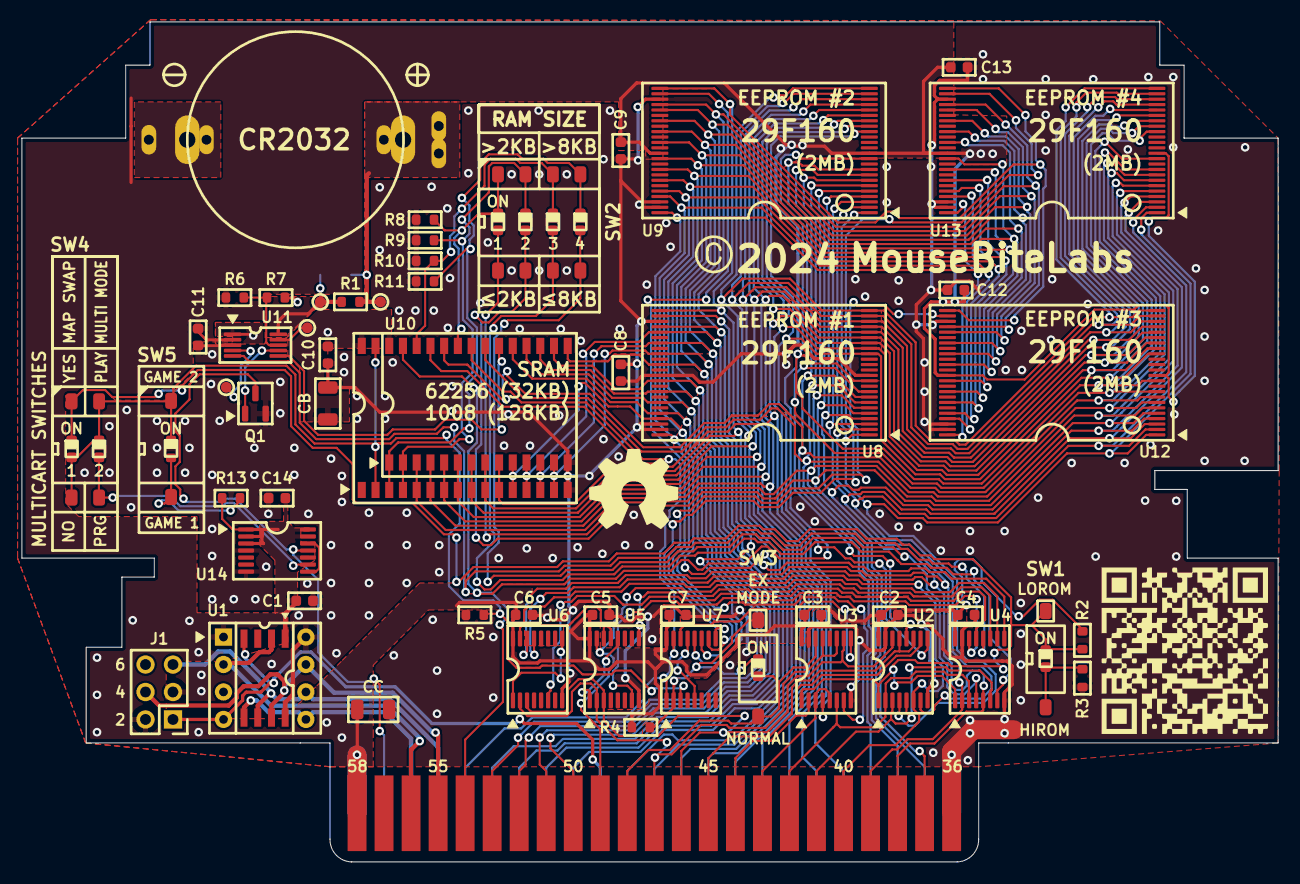
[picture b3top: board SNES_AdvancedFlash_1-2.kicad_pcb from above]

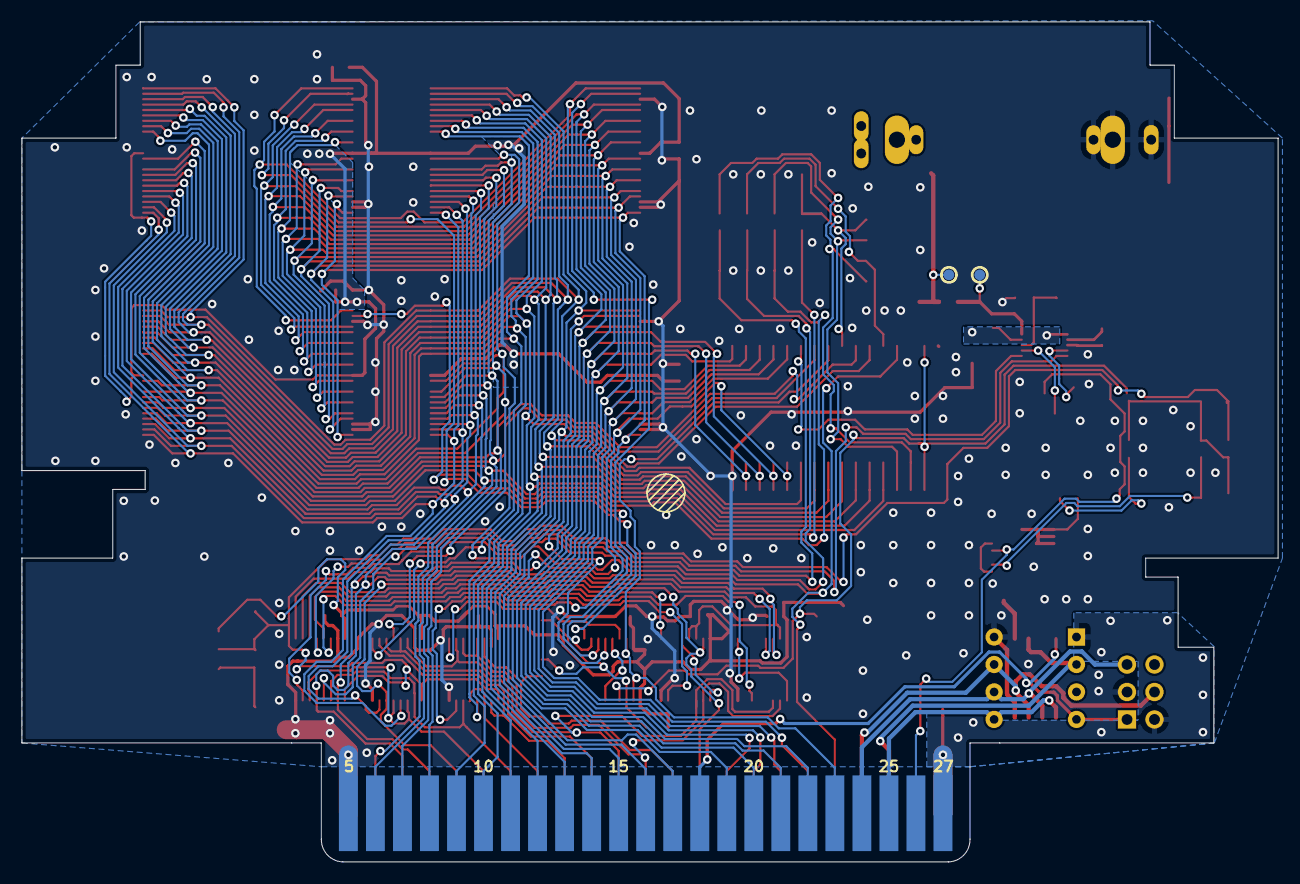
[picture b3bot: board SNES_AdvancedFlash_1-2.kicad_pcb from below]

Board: 2 copper layers, 116.2 x 77.7 mm, 67 parts (2 on the bottom side), 83 nets.

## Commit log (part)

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2025-11-20 Fix R4 value in BOM
2025-12-15 Update README.md
    Update coin cell part number
2025-12-15 Update README.md
    Updated coin cell part number
